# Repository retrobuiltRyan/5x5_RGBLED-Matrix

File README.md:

# 5x5_RGBLED-Matrix
25 NeoPixel SMD soldering activty / KiCAD layout learning example. 
LEDs= WS2812B 5050 RGB LED

BoM:
| Reference     | Value       | Qty | DigiKey / Supplier Link                             |
|---------------|-------------|-----|-----------------------------------------------------|
| C1–C6         | 1uF         | 6   | 1276-1068-1-ND                                       |
| LED1–LED25    | WS2812B     | 25  | [AliExpress Link](https://www.aliexpress.us/item/3256802466699315.html) |
| R1            | 220Ω        | 1   | RMCF1206FT220RCT-ND                                  |

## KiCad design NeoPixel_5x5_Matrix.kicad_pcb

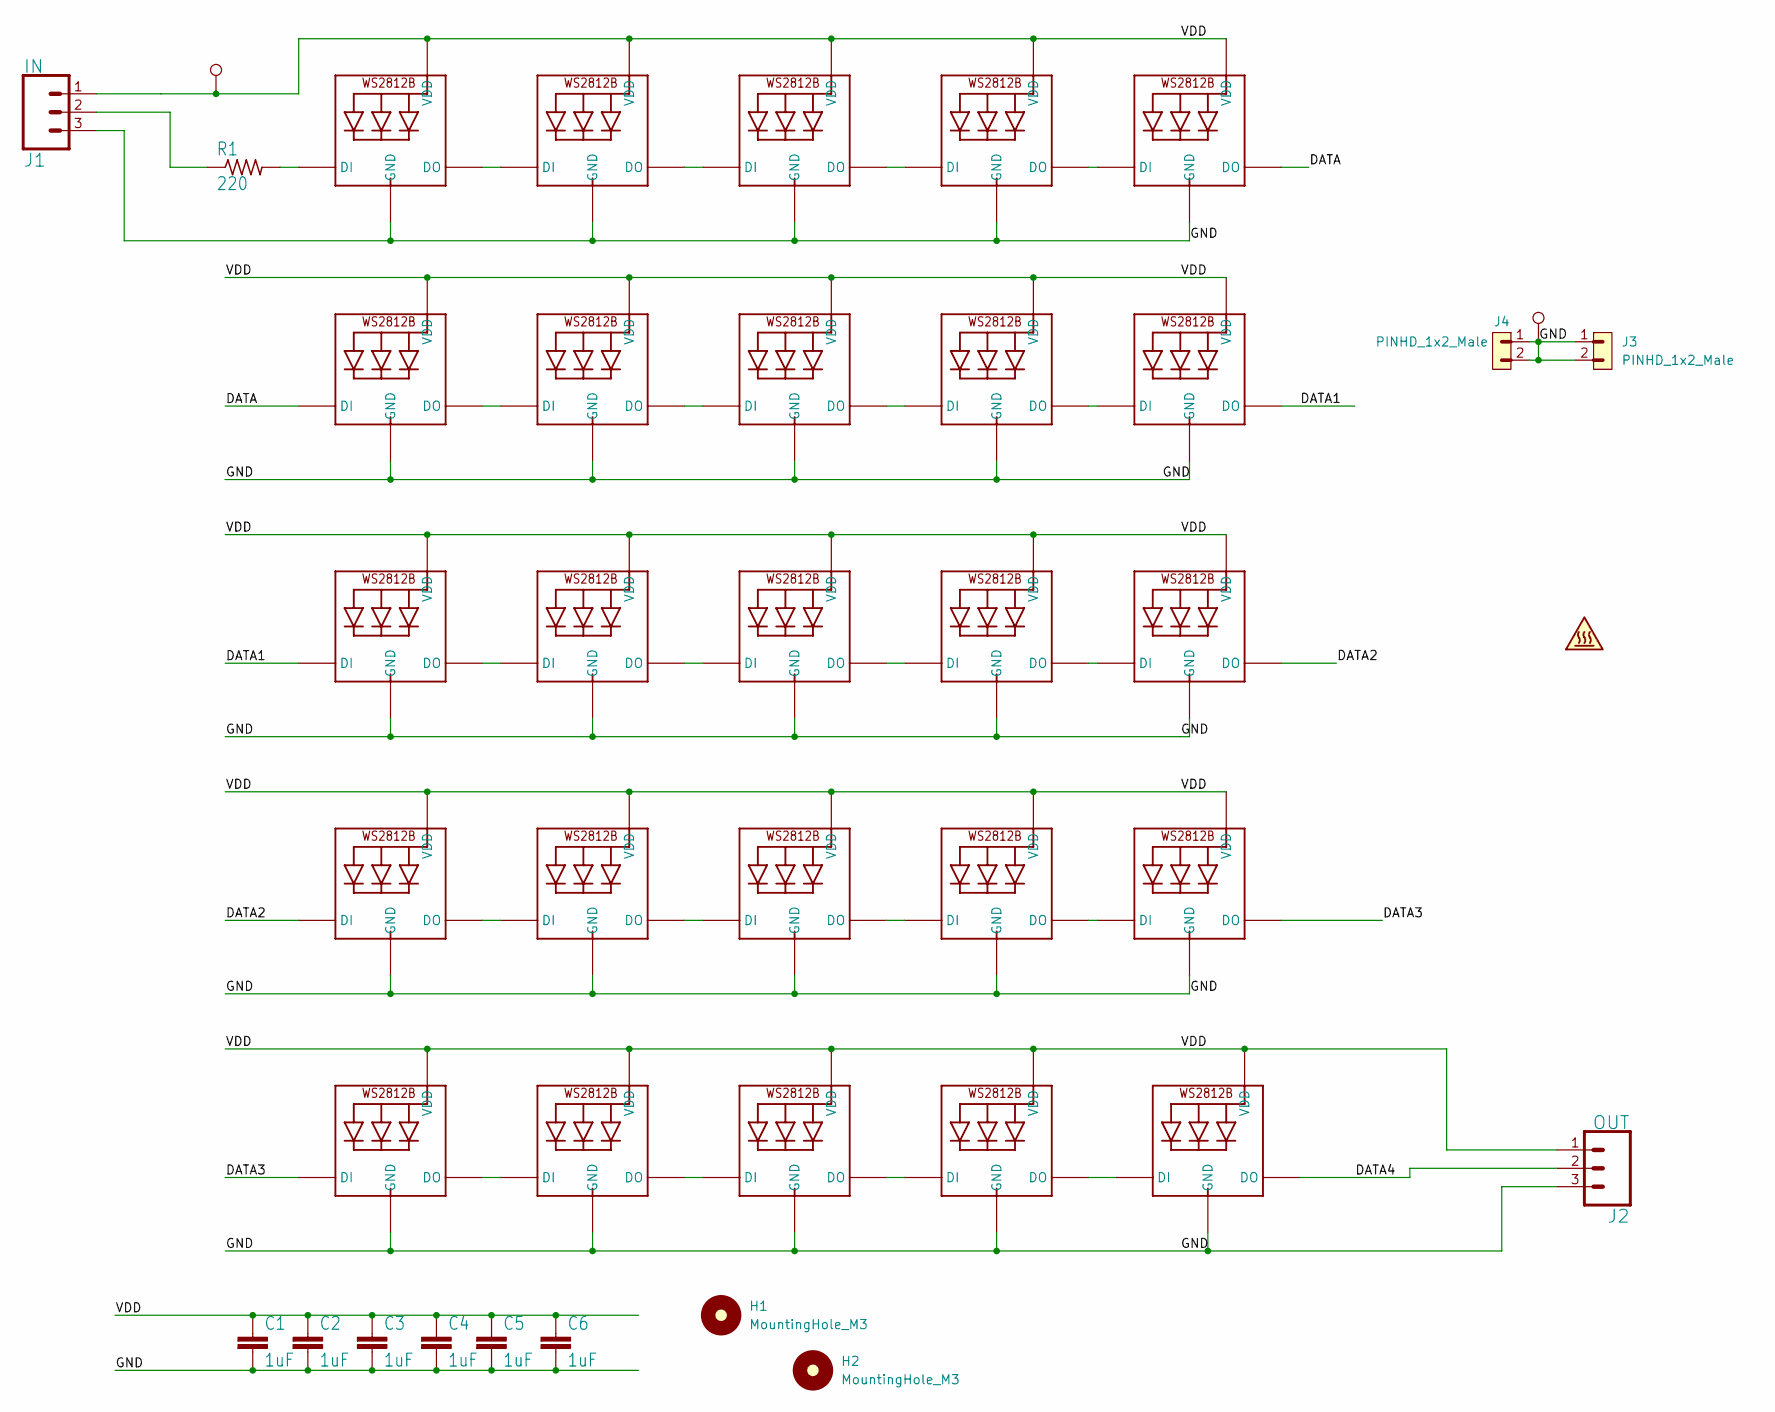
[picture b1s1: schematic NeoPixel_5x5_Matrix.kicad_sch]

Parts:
C1, C2, C3, C4, C5, C6: 1uF; C_1206_3216Metric; DigiKey P/N 1276-1068-1-ND
H1, H2: MountingHole_M3; MountingHole_3.2mm_M3
J1: IN; PinHeader_1x03_P2.54mm_Vertical
J2: OUT; PinHeader_1x03_P2.54mm_Vertical
J3, J4: PINHD_1x2_Male; PinHeader_1x02_P2.54mm_Vertical
LED1, LED2, LED3, LED4, LED5, LED6, LED7, LED8, LED9, LED10, LED11, LED12, LED13, LED14, LED15, LED16, LED17, LED18, LED19, LED20, LED21, LED22, LED23, LED24, LED25: WS2812B_5050N; LED_WS2812B_PLCC4_5.0x5.0mm_P3.2mm
R1: 220; R_1206_3216Metric; DigiKey P/N RMCF1206FT220RCT-ND
TP1, TP2: TestPoint; TestPoint_Pad_2.5x2.5mm

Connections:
/DATA: LED5.2 (DO), LED6.4 (DI)
/DATA1: LED10.2 (DO), LED11.4 (DI)
/DATA2: LED15.2 (DO), LED16.4 (DI)
/DATA3: LED20.2 (DO), LED21.4 (DI)
/DATA4: J2.2, LED25.2 (DO)
/GND: C1.2, C2.2, C3.2, C4.2, C5.2, C6.2, J1.3, J2.3, J3.1, J3.2, J4.1, J4.2, LED1.3 (GND), LED2.3 (GND), LED3.3 (GND), LED4.3 (GND), LED5.3 (GND), LED6.3 (GND), LED7.3 (GND), LED8.3 (GND), LED9.3 (GND), LED10.3 (GND), LED11.3 (GND), LED12.3 (GND), LED13.3 (GND), LED14.3 (GND), LED15.3 (GND), LED16.3 (GND), LED17.3 (GND), LED18.3 (GND), LED19.3 (GND), LED20.3 (GND), LED21.3 (GND), LED22.3 (GND), LED23.3 (GND), LED24.3 (GND), LED25.3 (GND), TP1.1
/VDD: C1.1, C2.1, C3.1, C4.1, C5.1, C6.1, J1.1, J2.1, LED1.1 (VDD), LED2.1 (VDD), LED3.1 (VDD), LED4.1 (VDD), LED5.1 (VDD), LED6.1 (VDD), LED7.1 (VDD), LED8.1 (VDD), LED9.1 (VDD), LED10.1 (VDD), LED11.1 (VDD), LED12.1 (VDD), LED13.1 (VDD), LED14.1 (VDD), LED15.1 (VDD), LED16.1 (VDD), LED17.1 (VDD), LED18.1 (VDD), LED19.1 (VDD), LED20.1 (VDD), LED21.1 (VDD), LED22.1 (VDD), LED23.1 (VDD), LED24.1 (VDD), LED25.1 (VDD), TP2.1
unnamed: J1.2, R1.1
unnamed: LED1.4 (DI), R1.2
unnamed: LED1.2 (DO), LED2.4 (DI)
unnamed: LED2.2 (DO), LED3.4 (DI)
unnamed: LED3.2 (DO), LED4.4 (DI)
unnamed: LED4.2 (DO), LED5.4 (DI)
unnamed: LED6.2 (DO), LED7.4 (DI)
unnamed: LED7.2 (DO), LED8.4 (DI)
unnamed: LED8.2 (DO), LED9.4 (DI)
unnamed: LED9.2 (DO), LED10.4 (DI)
unnamed: LED11.2 (DO), LED12.4 (DI)
unnamed: LED12.2 (DO), LED13.4 (DI)
unnamed: LED13.2 (DO), LED14.4 (DI)
unnamed: LED14.2 (DO), LED15.4 (DI)
unnamed: LED16.2 (DO), LED17.4 (DI)
unnamed: LED17.2 (DO), LED18.4 (DI)
unnamed: LED18.2 (DO), LED19.4 (DI)
unnamed: LED19.2 (DO), LED20.4 (DI)
unnamed: LED21.2 (DO), LED22.4 (DI)
unnamed: LED22.2 (DO), LED23.4 (DI)
unnamed: LED23.2 (DO), LED24.4 (DI)
unnamed: LED24.2 (DO), LED25.4 (DI)

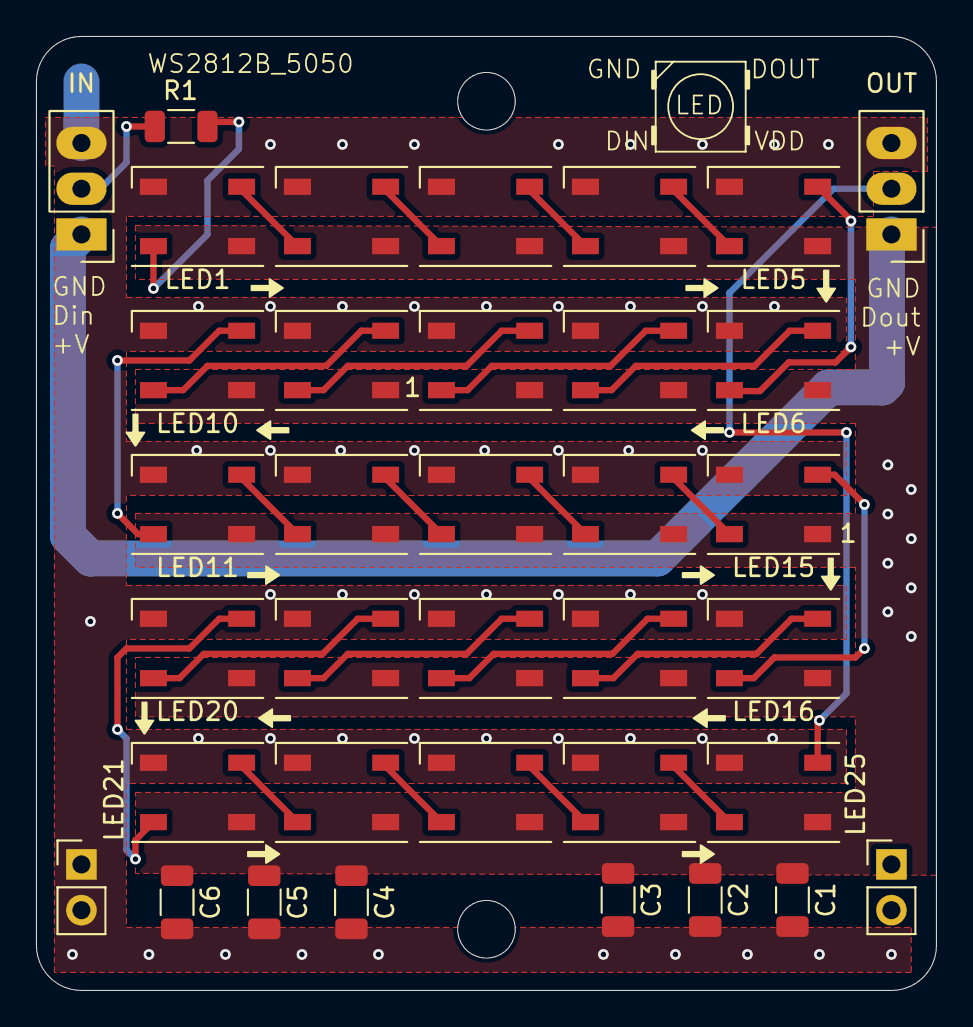
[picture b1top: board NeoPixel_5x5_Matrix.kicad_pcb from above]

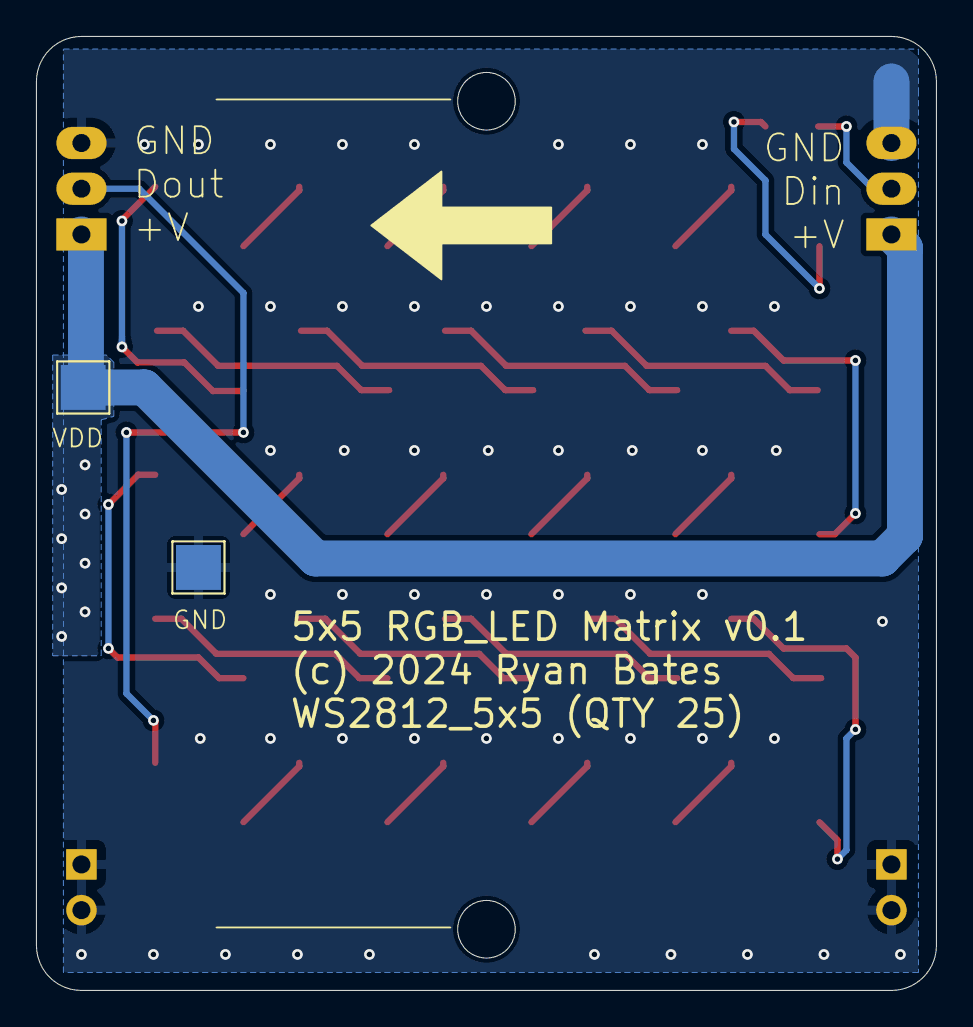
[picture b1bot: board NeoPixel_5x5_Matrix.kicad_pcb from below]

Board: 2 copper layers, 50.0 x 53.0 mm, 40 parts (2 on the bottom side), 29 nets.

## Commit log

2025-07-30 Design Files
    KiCAD
2025-07-30 Gerbers
    JLCPCB

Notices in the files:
NeoPixel_5x5_Matrix.kicad_pcb:
(c) 2024 Ryan Bates
